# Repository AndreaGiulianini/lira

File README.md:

# Lira

> [!WARNING]
> **This keyboard has never been built.** It is a design only: no prototype of either version (wireless on branch
> `main`, wired on branch `rp2040`) has ever been ordered, assembled or powered on, and nothing here has been tested
> on real hardware. The circuit, PCB, case and firmware are generated and checked automatically and reviewed on paper,
> but passing those checks does not make a working board: there may be mistakes that only a real prototype would
> reveal. **Do not put it into production, sell it or order it in quantity.** If you build one anyway, treat it as an
> untested design: order the minimum quantity and expect to debug it yourself.

A 40% keyboard in the [KBDfans Agar Mini](https://kbdfans.com/products/agar-mini) layout, with a numpad on the
left and a split 3u + 3u spacebar.
USB-C, hot-swap MX switches, RMK firmware with Vial, and a built-in USB sound card (3.5 mm headset jack
at the back: headphones and microphone, with a headphone amplifier). 3D-printed case inspired by the Apple
M0110 (1984), top mount: the plate is screwed to the top frame and the PCB hangs from the switches, so no printed
part has to hold the PCB flat.

**Two versions of the same keyboard**, one per git branch, with the same layout, plate and sound card, and the same case and keymap apart from the battery pocket and the Bluetooth keys:

| Branch | Version | Microcontroller | Power |
|---|---|---|---|
| [`main`](../../tree/main) | wireless: Bluetooth + USB-C | Ebyte E73 module (nRF52840) | LiPo battery, or the cable alone |
| **`rp2040`** (this one) | **wired: USB-C only** | **Raspberry Pi RP2040** + 16 MB QSPI flash | **the cable, no battery** |

The sound card only ever works over the cable (there is no audio over Bluetooth here), so if the headset jack is
the point, the radio, the cell, the charger and the power switch are things you pay for and never use: this
version drops them. It is also simpler to build: the RP2040 programs itself over USB (no SWD probe, no bootloader
to flash), and there is no battery to buy and wire.

## Inspiration and credits

None of the ideas here are mine: this board is a combination of things other people made, plus the one thing I
always wanted and could not buy — a headset jack on a keyboard.

- **Layout** — the 40% block with the split 3u + 3u spacebar is KBDfans' [Agar Mini](https://kbdfans.com/products/agar-mini).
  The numpad on the left is my addition, and what makes it 57 keys.
- **Board** — the "40% + numpad in one flat rectangular case" idea and the overall proportions are inspired by the
  [**Lyra**](https://github.com/PiKeeb/lyra-keyboard), designed by **alexbarb** (case) with the PCB by **KGOH** and
  **ILWrites**. Lira is not a copy: it uses the Agar Mini body, a top-mount case and a completely different PCB.
- **The 3.5 mm headset jack** — laptop headphones + microphone built into the keyboard itself. The sound card follows
  C-Media's own CM108B reference design behind a CH334P USB hub (see
  `production/5-schematic-and-checks/differences-from-wireless.txt`).
- **Microcontroller** — Raspberry Pi's own minimum circuit for the RP2040 ("Hardware design with RP2040", the
  Pico's): crystal, flash, decoupling, BOOT and RESET. The wireless version's power, USB and programming follow the
  BlueMicro840 ([jpconstantineau/NRF52-Board](https://github.com/jpconstantineau/NRF52-Board)).
- **Case** — the shape and colour follow the Apple M0110 (1984).

Thanks to all of them.

## Where to find things

| Folder | What it contains |
|---|---|
| **[`production/`](production/README.md)** | Everything to build the 57-key keyboard: files for JLCPCB, plate, case to print, firmware, pictures |
| [`guide/`](guide/build-guide.md) | Complete guide: ordering from JLCPCB, what to buy, first programming, printing and assembly |
| [`source/`](source/README.md) | The code that generates everything: edit only here, then regenerate |

`production/` is **self-contained**: it holds everything needed to build the keyboard (the KiCad files use the footprint libraries in `source/lib/`)
and has its own README listing the files and what to do with them:

```
production/
├── README.md                what's inside and what to do with it
├── 1-pcb-jlcpcb/            gerber-pcb.zip, bom.csv, cpl.csv
├── 2-plate/                 the plate: JLCPCB (FR4 gerbers), laser cut (DXF) or 3D printed (2 STL)
├── 3-case-3d-print/         the 4 STL pieces (+ step/)
├── 4-firmware/              .uf2 firmware, vial.json, keyboard.toml
├── 5-schematic-and-checks/  schematic (PDF) and the results of the automatic checks
├── kicad/                   PCB, plate and schematic to open in KiCad
└── images/                  layout, Blender renders: on a desk, every side, exploded, PCB
```

> `production/` is **rewritten** on every regeneration: do not edit it by hand.

## How reliable it is

Everything below is checked on paper and in software, **not a tested board** (see the warning at the top).

The RP2040 circuit is Raspberry Pi's minimal design (the Pico's), with the crystal Raspberry Pi qualified for it;
everything else is the wireless board's (USB-C, ESD, hub, sound card, matrix). The differences are listed in
`5-schematic-and-checks/differences-from-wireless.txt`. The circuit, PCB, case and firmware are checked
automatically on every build:

- KiCad's ERC, a pin-by-pin check between circuit, PCB and schematic, and datasheet tests written independently of
  the design (`erc-kicad.txt`, `consistency-check.txt`, `datasheet-checks.txt`);
- a mechanical fit check of the case against the finished PCB (`fit-check.txt`).

These checks reduce the risk; they do not replace a prototype. The guide, §8, lists what to verify on the first
board.

## Small hardware

| Item | Quantity |
|---|---|
| M2 heat-set inserts (for a 3.2 mm hole, length 3 mm) | 6 (top frame: the plate's ears) |
| M2 × 5 mm socket-head screws (DIN 912) | 6 (plate to top frame) |
| Short M3 heat-set inserts (Ø ~4.5 mm, length 3 mm, for a 4.0 mm hole) | 11 (top frame) |
| M3 × 12 mm socket-head screws (DIN 912) | 8 (front and sides) |
| M3 × 20 mm socket-head screws (DIN 912) | 3 (back: through the PCB's holes and the plate's tabs) |
| Ø 3 × 14 mm alignment pins (steel rod or 3 mm filament) | 4 |
| Ø 12 mm rubber feet | 4 |
| Long 2.5 mm hex key (some M3 screw holes are 21 mm deep) and a 1.5 mm hex key (M2) | 1 + 1 |

## Printing the case

- No supports. **Top frames**: lying on their flat underside (the side the plate screws to), deck up: the STL files are exported tilted, as assembled, so use the slicer's “lay on face” on that flat underside. **Bottom halves**: placed the way they sit
  on the desk.
- PLA or PETG, 3 perimeters, 5 solid top layers and 4 bottom layers. Infill: **top frames** gyroid 15 %,
  **bottom halves** gyroid 8 % or lightning. The strength comes from the walls and the solid layers, not from
  the inside.
- Material (estimate, PLA): about 300–320 g this way, versus about 370 g with 15 % everywhere. The bottom halves
  are already 85 % empty inside: designing cavities into them would cost **more** (tried it: 290 g instead of
  273 g), because every cavity adds walls, a ceiling and ribs that print solid.
- For the fine texture of the M0110: light "fuzzy skin" (0.1 mm) on the outer surfaces, or textured spray
  paint.
- Reference colour: warm beige between `#C8C2A0` and `#D5D0B4` (Pantone 453 was the original).
- The case is split to fit a 256 mm bed: with a bigger printer, change `BED` in
  `source/case/gen_case.py` and regenerate.

## Editing and regenerating

Edit only `source/` (for example `layout.py` for the keys, `case/gen_case.py` for the case), then:

```sh
cd source
make all            # regenerates everything (about 25 minutes on an M4, most of it the Blender renders)
make pcb            # or a single step: see source/README.md
```

Technical details in [`source/README.md`](source/README.md).

## License

[MIT](LICENSE) — that covers everything in this repository that I made.

The firmware is built on [RMK](https://github.com/HaoboGu/rmk) and the embassy crates (MIT / Apache-2.0) and is configured with [Vial](https://get.vial.today) (GPL-2.0, used, not bundled).

Bundled third-party parts keep their own terms and are **not** relicensed by the above: `source/tools/KeyV2`
(GPL-3.0, a git submodule), Raspberry Pi's second-stage boot code in the firmware (BSD-3-Clause), the kiswitch footprints and 3D models under `source/lib/` (CC BY-SA 4.0), and the
vendor symbols/models (KiCad, LCSC). The [Lyra](https://github.com/PiKeeb/lyra-keyboard) and the KBDfans Agar Mini
are cited as inspiration only — no files from either are included here.

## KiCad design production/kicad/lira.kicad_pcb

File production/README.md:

# Lira

57 keys: numpad on the left + Agar mini 40% with a split 3u + 3u spacebar, built-in USB sound card. Wired version: USB-C only, no battery, Raspberry Pi RP2040.

> [!WARNING]
> **This keyboard has never been built.** It is a design only: no prototype of either version (wireless on branch
> `main`, wired on branch `rp2040`) has ever been ordered, assembled or powered on, and nothing here has been tested
> on real hardware. The circuit, PCB, case and firmware are generated and checked automatically and reviewed on paper,
> but passing those checks does not make a working board: there may be mistakes that only a real prototype would
> reveal. **Do not put it into production, sell it or order it in quantity.** If you build one anyway, treat it as an
> untested design: order the minimum quantity and expect to debug it yourself.

> This folder is **generated automatically** from `../source/` and is rewritten every time it is regenerated:
> do not edit it by hand.

## What is here and what to do with it

| Folder | Files | What to do with them |
|---|---|---|
| `1-pcb-jlcpcb/` | `gerber-pcb.zip`, `bom.csv`, `cpl.csv` | PCB order at JLCPCB: 2 layers, 1.6 mm, assembly of the **bottom side** (206 parts, 44 different part numbers). |
| `2-plate/` | | The plate carries the keyboard (6 ears and 3 back tabs screw it to the top frame). Three ways to make it, all interchangeable (guide, §2): |
| | `jlcpcb/gerber-plate.zip` | cut by JLCPCB: 1.6 mm FR4, ordered like a PCB with no copper and no assembly (black or white) |
| | `laser-cut/plate.dxf` | laser cut in metal or plastic (1.5 mm aluminium or steel, POM…), e.g. JLCCNC sheet metal |
| | `3d-print/plate-left.stl`, `plate-right.stl` | 3D printed (PLA/PETG) in two pieces, top face on the bed, no supports; 4 mm ribbed, 1.5 mm where the switches clip in |
| `3-case-3d-print/` | `bottom-left.stl`, `bottom-right.stl`, `top-left.stl`, `top-right.stl` | Case to print **without supports**: the top frames lying on their flat underside (the side the plate screws to), deck up: the STL files are exported tilted, as assembled, so use the slicer's “lay on face” on that flat underside, the bottom halves the way they sit on the desk. The same pieces for CAD are in `step/` |
| | `fit-check.txt` | Result of the automatic fit check: PCB, parts, plate, keys, screws and ports against the printed pieces (see guide, §7) |
| `4-firmware/` | `lira.uf2` | Firmware: a new board shows up as the **RPI-RP2** drive as soon as it is plugged in: drag the file onto it. To update it later: fn + Esc, or hold BOOT (paperclip, underside) while plugging the cable in (see guide §4) |
| | `vial.json`, `keyboard.toml` | Configuration (Vial reads it from the keyboard by itself; these are for reference only) |
| `5-schematic-and-checks/` | `schematic.pdf` | Circuit diagram, for anyone who wants to review the circuit (also `schematic.svg`) |
| | `differences-from-wireless.txt` | What changes from the wireless board (RP2040 after Raspberry Pi's own design, no battery), and the sound card's differences from the chip maker's reference design |
| | `erc-kicad.txt`, `consistency-check.txt`, `datasheet-checks.txt` | Results of the three automatic checks (see guide, §6) |
| | `netlist.json` | Every connection, pin by pin, in readable form |
| `kicad/` | `lira.kicad_pcb`, `plate.kicad_pcb`, `schematic/` | To open the PCB, plate and schematic in KiCad |
| `images/` | pictures | Layout; Blender Cycles renders: the keyboard on a desk (`desk.jpg`), the case from every side, an exploded view, the PCB |

## Summary

- 57 hot-swap MX switches, USB-C, Raspberry Pi RP2040, RMK firmware with Vial. Wired: no battery, no Bluetooth (the
  wireless version, with an nRF52840 and a LiPo cell, is on the git branch `main`).
- Built-in USB sound card: a 3.5 mm headset jack at the back (headphones + microphone, CTIA plugs) with a headphone
  amplifier, behind a USB hub; over the USB cable the computer sees a keyboard and a USB headset (no drivers). The
  firmware turns it on once the computer has set the keyboard up, and the amplifier off while the computer sleeps and
  as soon as the cable starts to be pulled out (no click).
- Case in 4 pieces to print (256 mm bed), inspired by the Apple M0110; top mount (plate screwed to the top frame).

## Buy separately

| What | Notes |
|---|---|
| 57 MX switches + keycaps (Agar mini set + numpad kit) | you need a 2u vertical Enter, a 2u 0, a 1u + and a 1u − (most numpad kits only have a 2u +) |
| Screw-in PCB stabilizers: 2 × 2u + 2 for the 3u bars | 3u wire with 38.1 mm spacing |
| Screws, heat-set inserts, pins, feet | list in `../README.md` |

Every step in detail: [`../guide/build-guide.md`](../guide/build-guide.md).

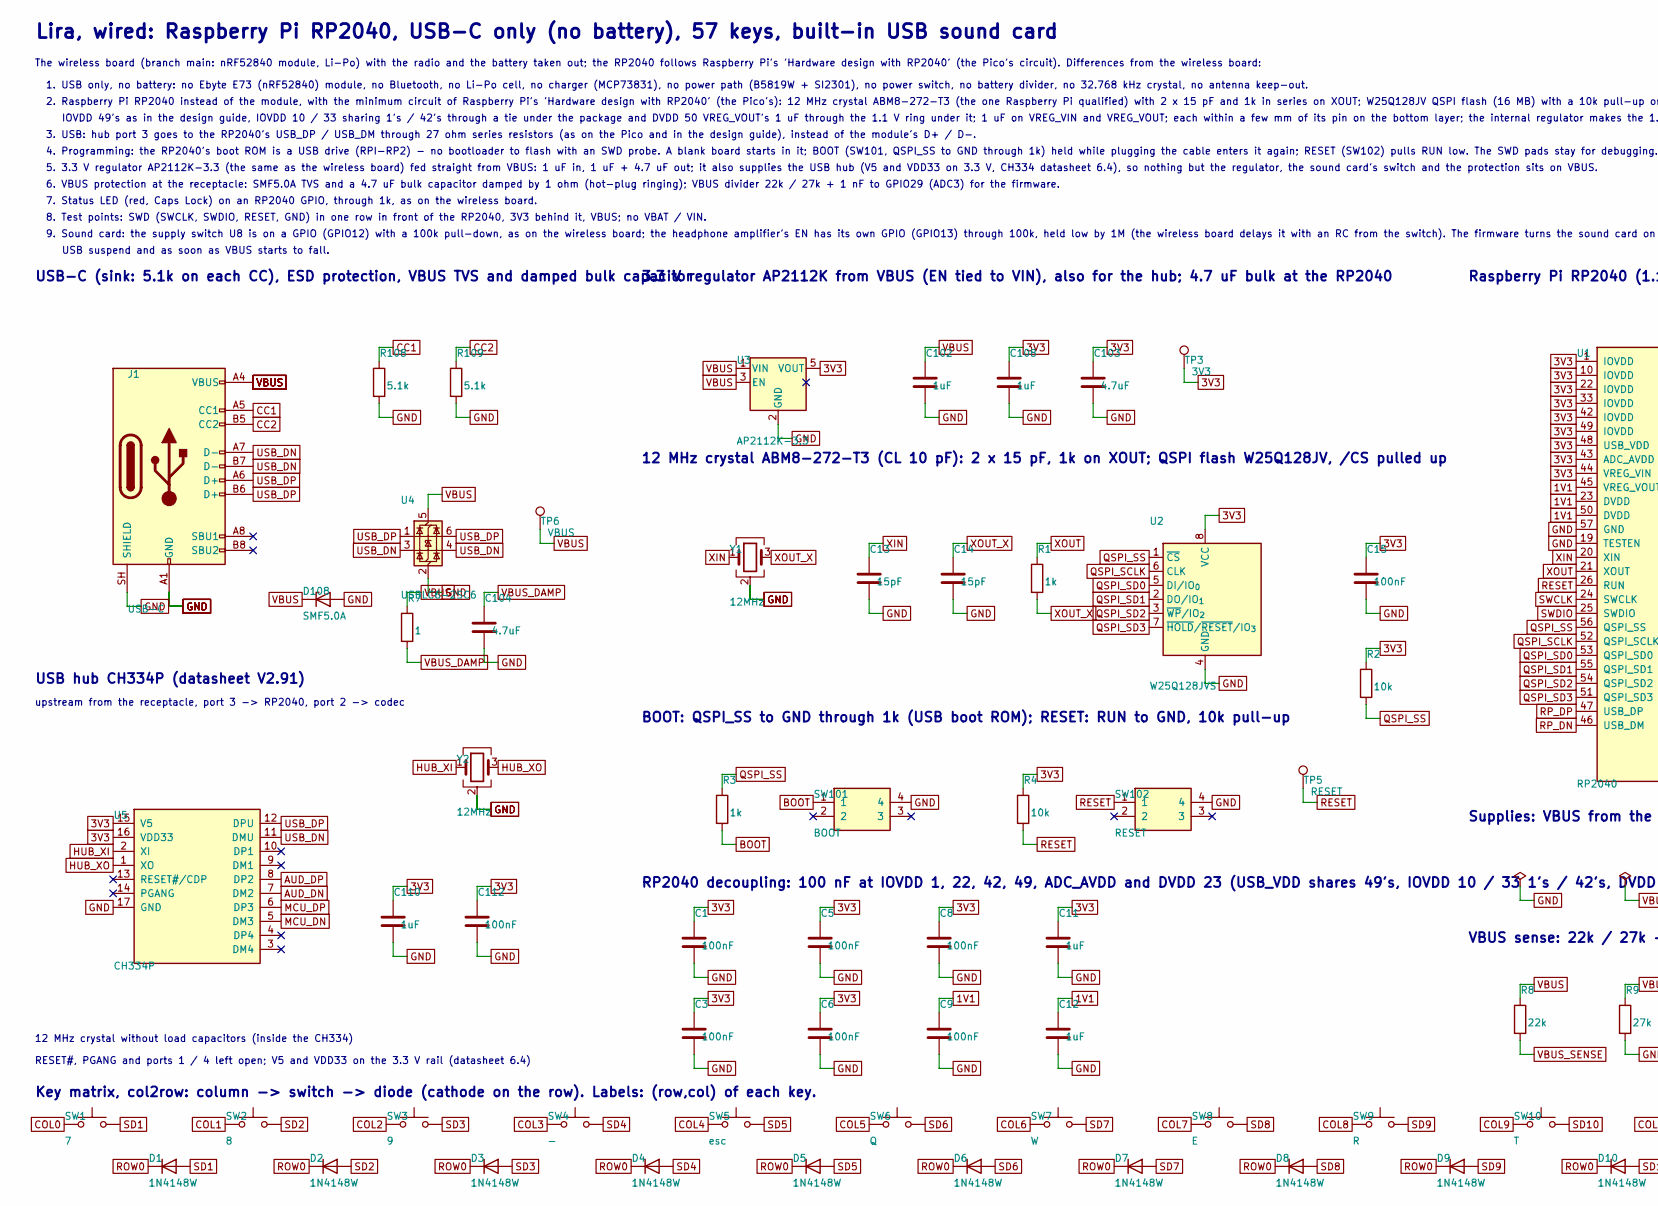
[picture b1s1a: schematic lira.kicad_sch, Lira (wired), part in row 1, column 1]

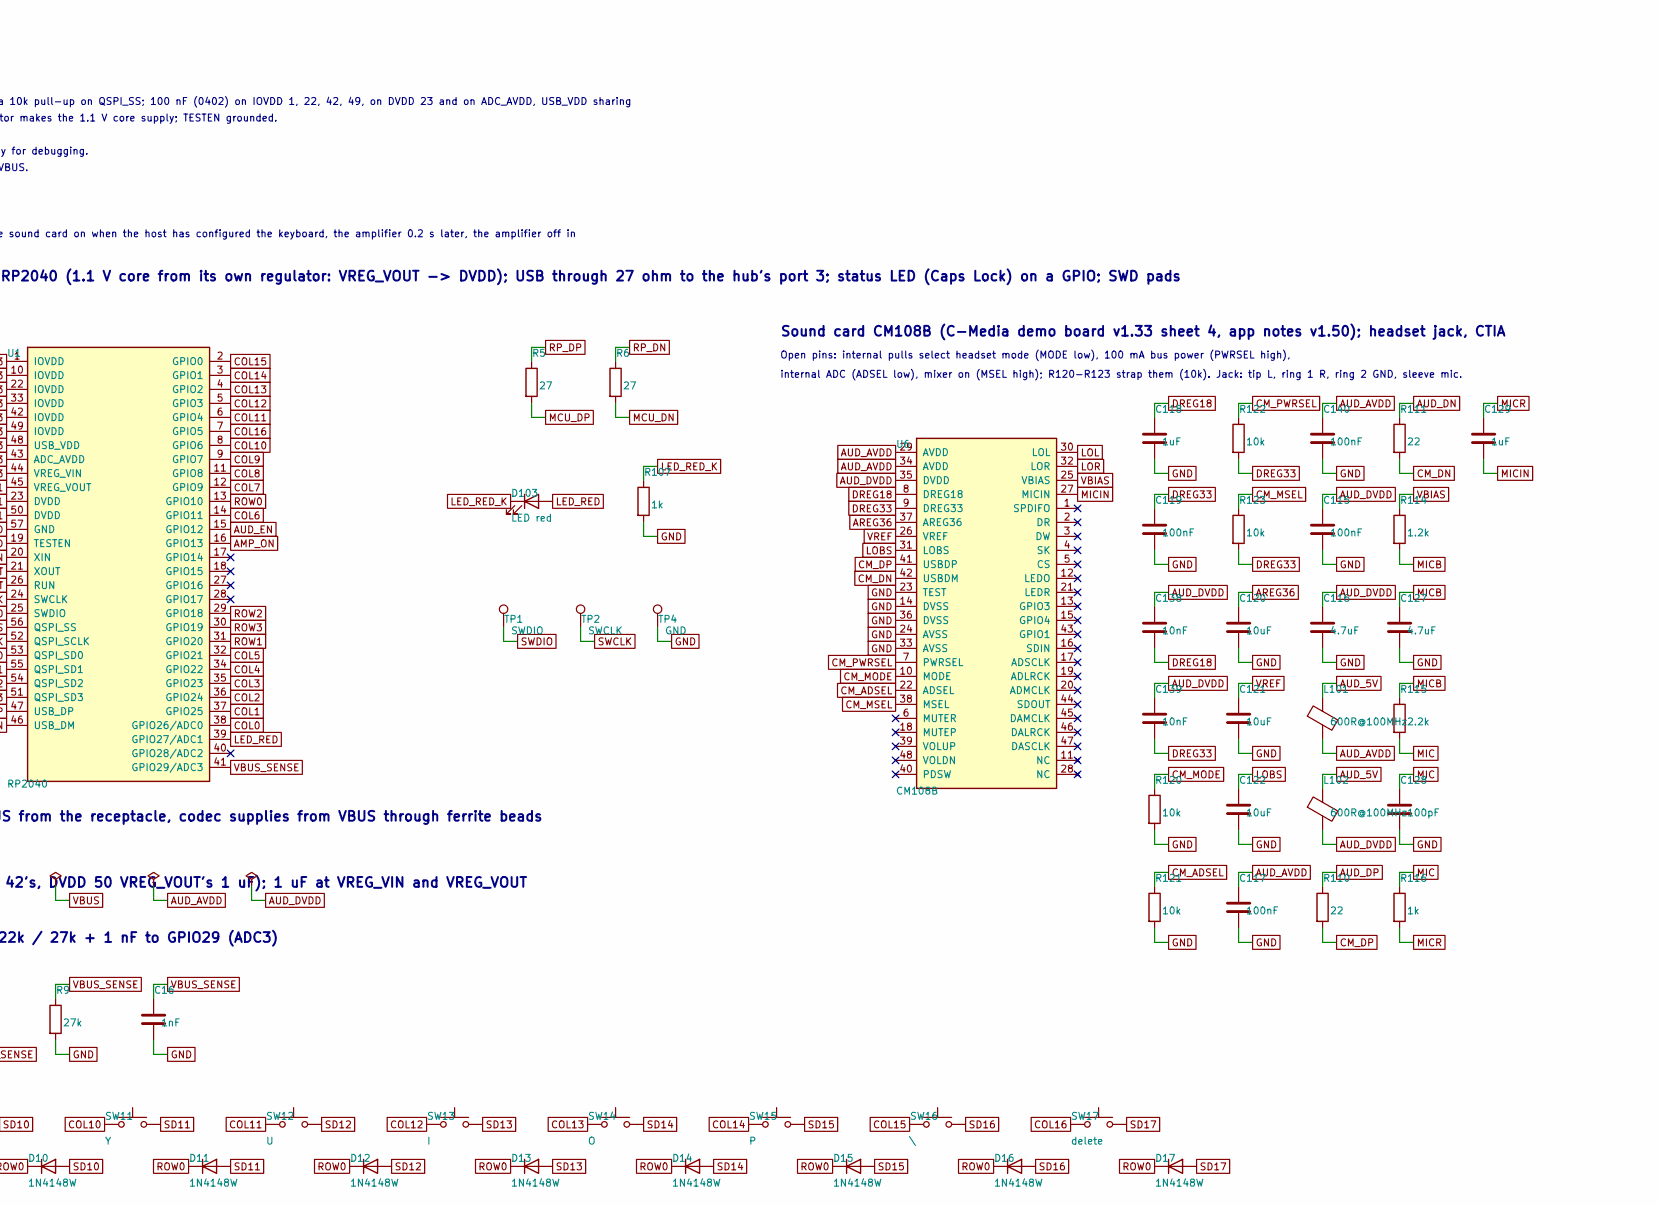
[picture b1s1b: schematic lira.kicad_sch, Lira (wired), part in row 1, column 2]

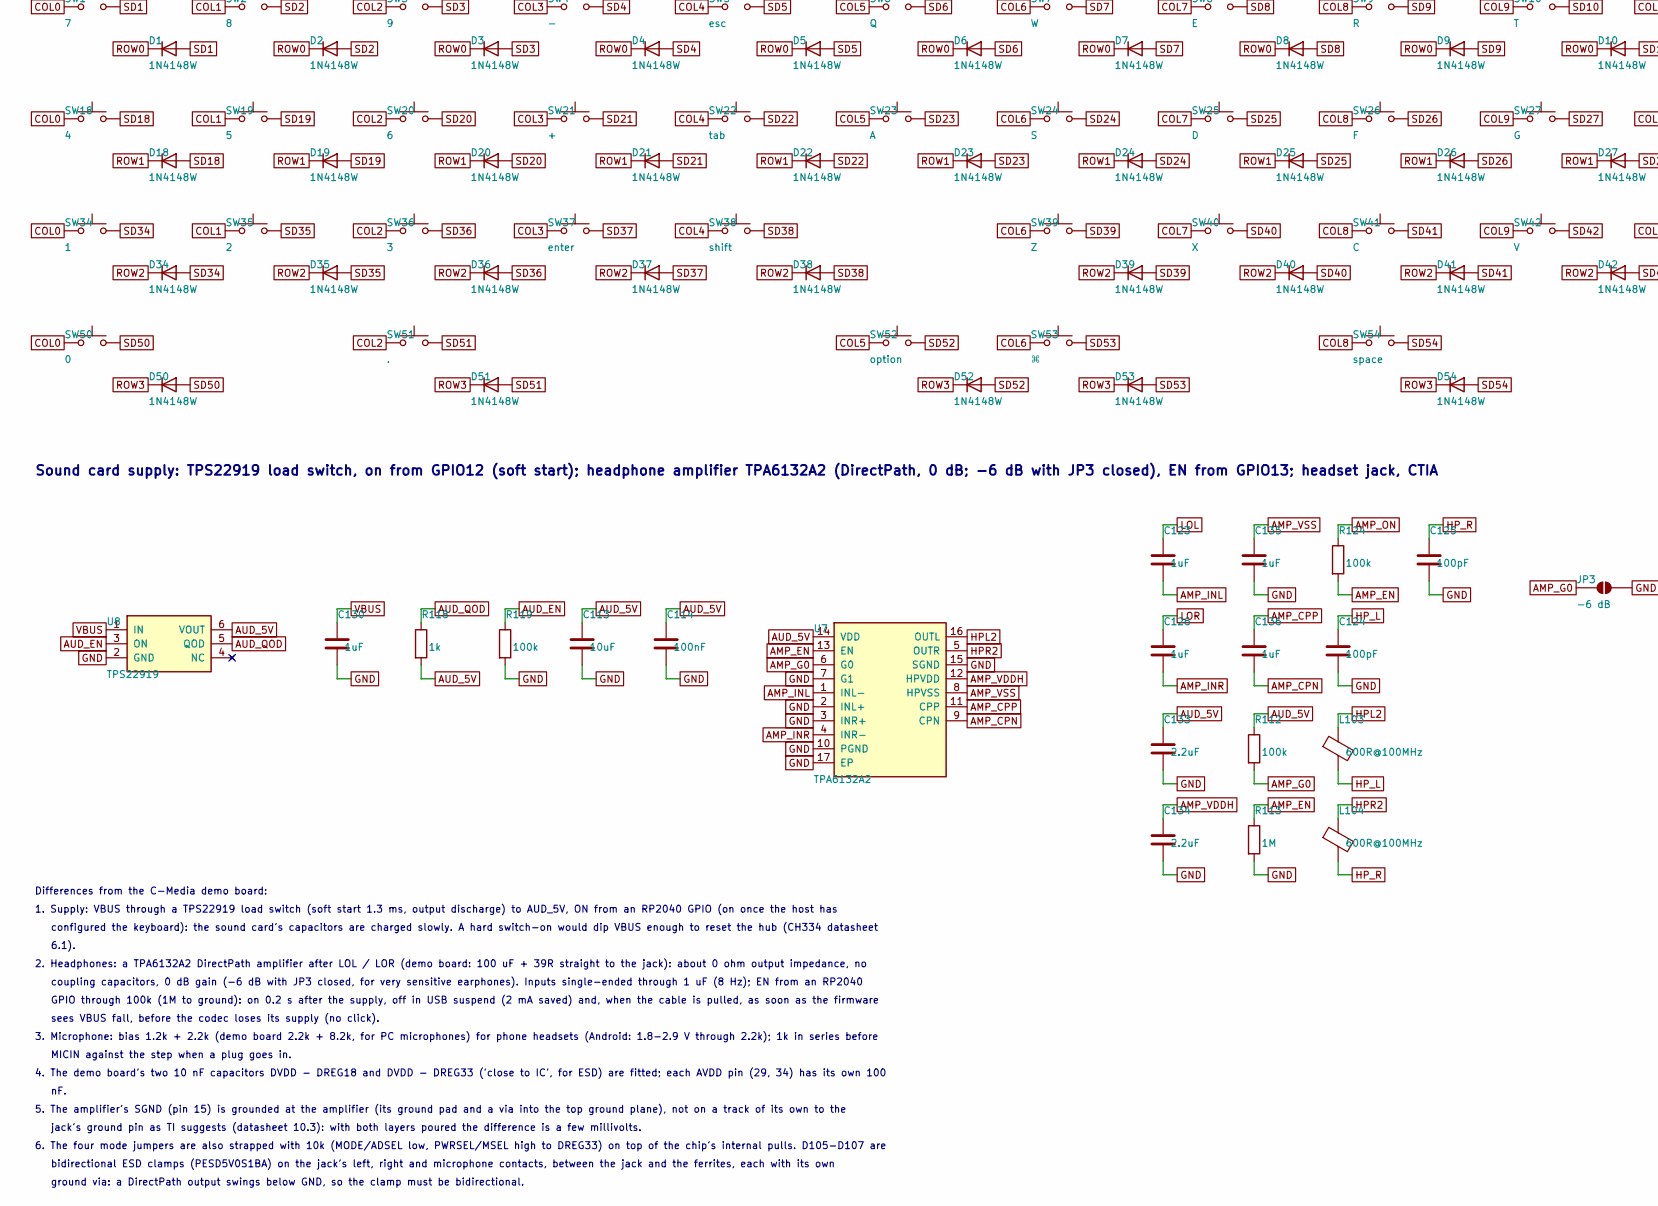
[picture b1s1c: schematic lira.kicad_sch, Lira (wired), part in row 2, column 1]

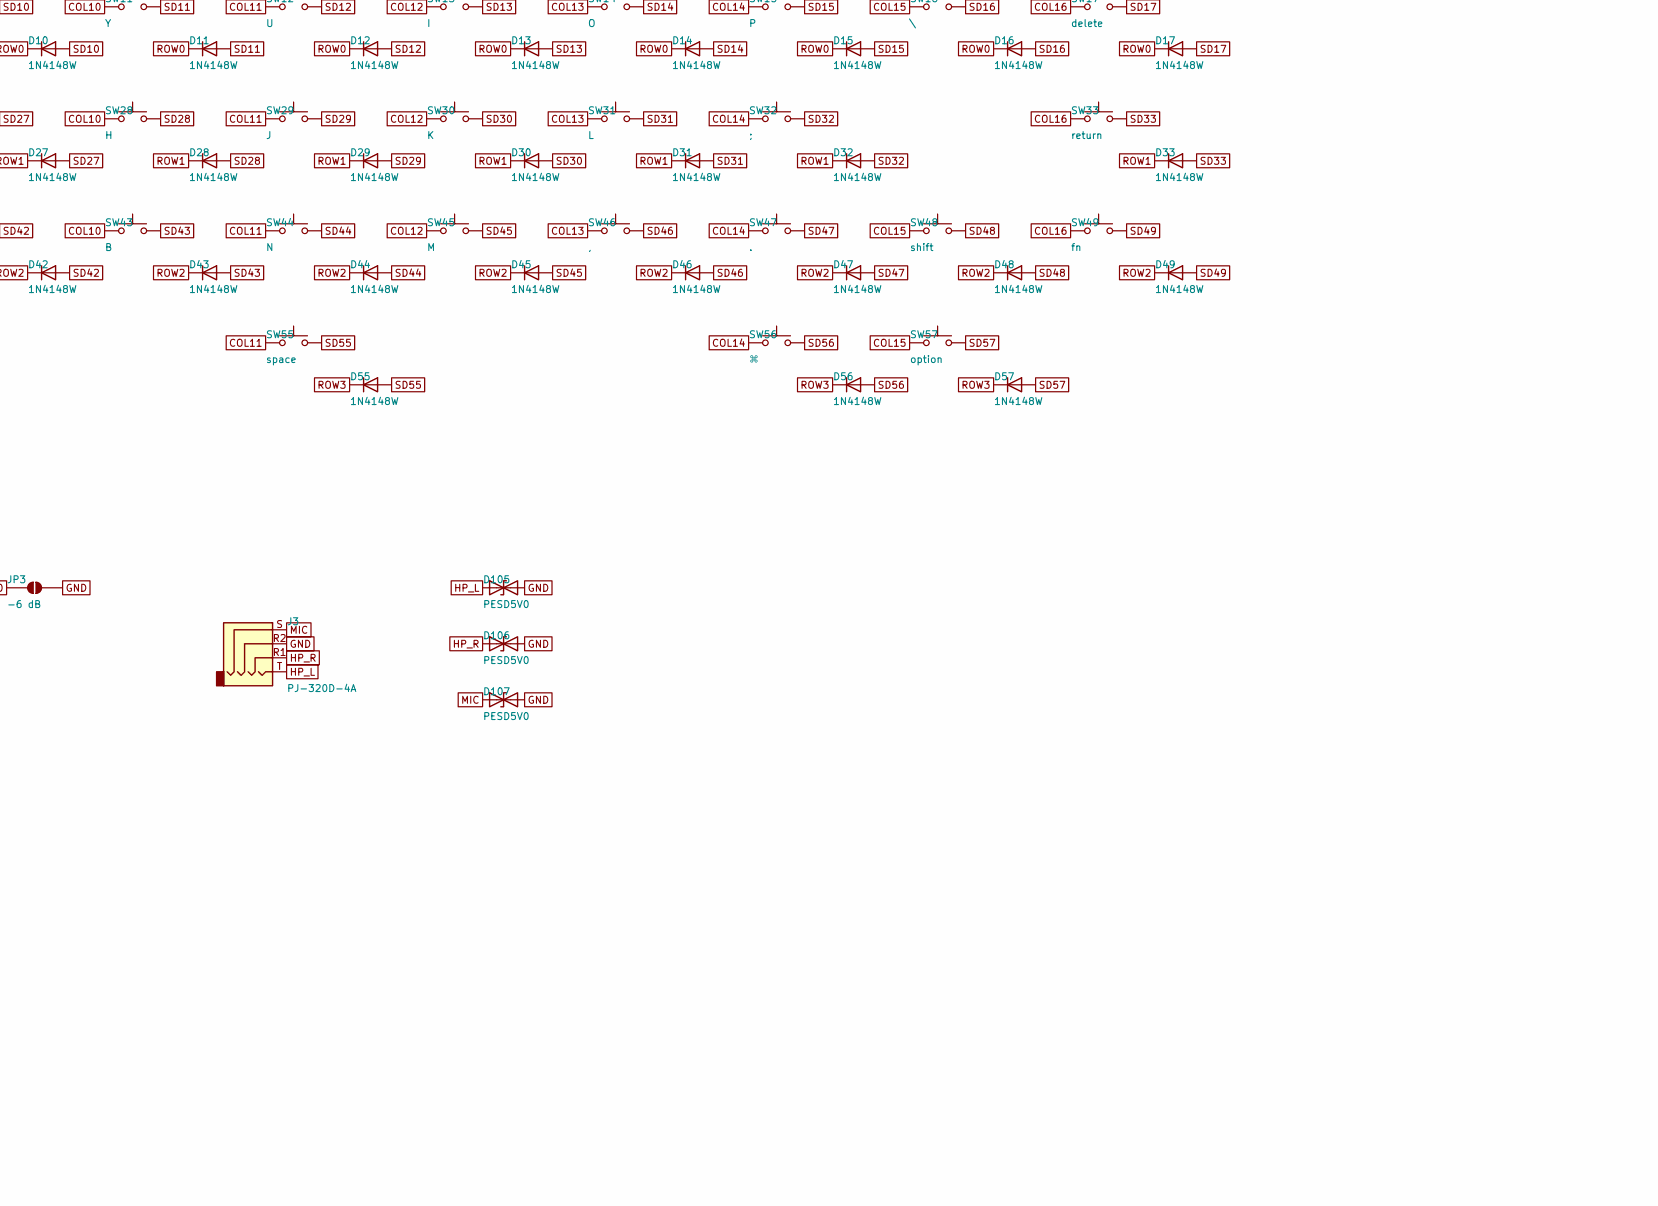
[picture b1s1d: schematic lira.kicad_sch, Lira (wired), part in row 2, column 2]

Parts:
C1, C3, C5, C6, C8, C9, C140: 100nF; C_0402_1005Metric; LCSC C1525
C11, C12: 1uF; C_0402_1005Metric; LCSC C52923
C13, C14: 15pF; C_0402_1005Metric; LCSC C1548
C15, C112, C114, C115, C117, C119: 100nF; C_0603_1608Metric; LCSC C14663
C16: 1nF; C_0603_1608Metric; LCSC C1588
C102, C108, C110, C118, C123, C126, C129, C130, C135, C136: 1uF; C_0603_1608Metric; LCSC C15849
C103, C116, C127: 4.7uF; C_0603_1608Metric; LCSC C19666
C104: 4.7uF; C_0805_2012Metric; LCSC C1779
C113, C120, C121, C122: 10uF; C_0603_1608Metric; LCSC C19702
C124, C125, C128: 100pF; C_0603_1608Metric; LCSC C14858
C133, C134: 2.2uF; C_0603_1608Metric; LCSC C23630
C138, C139: 10nF; C_0603_1608Metric; LCSC C57112
D1, D2, D3, D4, D5, D6, D7, D8, D9, D10, D11, D12, D13, D14, D15, D16, D17, D18, D19, D20, D21, D22, D23, D24, D25, D26, D27, D28, D29, D30, D31, D32, D33, D34, D35, D36, D37, D38, D39, D40, D41, D42, D43, D44, D45, D46, D47, D48, D49, D50, D51, D52, D53, D54, D55, D56, D57: 1N4148W; D_SOD-123; LCSC C81598
D103: LED red; LED_0603_1608Metric; LCSC C2286
D105, D106, D107: PESD5V0; D_SOD-323; LCSC C19224
D108: SMF5.0A; D_SOD-123F; LCSC C2857263
J1: USB-C; USB_C_Receptacle_HRO_TYPE-C-31-M-12; LCSC C165948
J3: PJ-320D-4A; Jack_3.5mm_KoreanHropartsElec_PJ-320D-4A_Horizontal; LCSC C95562
JP3: -6 dB; SolderJumper-2_P1.3mm_Open_RoundedPad1.0x1.5mm
L101, L102, L103, L104: 600R@100MHz; L_0603_1608Metric; LCSC C1002
R1: 1k; R_0402_1005Metric; LCSC C11702
R2, R4, R120, R121, R122, R123: 10k; R_0603_1608Metric; LCSC C25804
R3, R107, R116, R118: 1k; R_0603_1608Metric; LCSC C21190
R5, R6: 27; R_0402_1005Metric; LCSC C2909343
R7: 1; R_0603_1608Metric; LCSC C22936
R8: 22k; R_0603_1608Metric; LCSC C31850
R9: 27k; R_0603_1608Metric; LCSC C22967
R108, R109: 5.1k; R_0603_1608Metric; LCSC C23186
R110, R111: 22; R_0603_1608Metric; LCSC C23345
R112, R119, R124: 100k; R_0603_1608Metric; LCSC C25803
R113: 1M; R_0603_1608Metric; LCSC C22935
R114: 1.2k; R_0603_1608Metric; LCSC C22765
R115: 2.2k; R_0603_1608Metric; LCSC C4190
SW1: 7; SW_Hotswap_Kailh_MX_1.00u; LCSC C41430893
SW2: 8; SW_Hotswap_Kailh_MX_1.00u; LCSC C41430893
SW3: 9; SW_Hotswap_Kailh_MX_1.00u; LCSC C41430893
SW4: −; SW_Hotswap_Kailh_MX_1.00u; LCSC C41430893
SW5: esc; SW_Hotswap_Kailh_MX_1.00u; LCSC C41430893
SW6: Q; SW_Hotswap_Kailh_MX_1.00u; LCSC C41430893
SW7: W; SW_Hotswap_Kailh_MX_1.00u; LCSC C41430893
SW8: E; SW_Hotswap_Kailh_MX_1.00u; LCSC C41430893
SW9: R; SW_Hotswap_Kailh_MX_1.00u; LCSC C41430893
SW10: T; SW_Hotswap_Kailh_MX_1.00u; LCSC C41430893
SW11: Y; SW_Hotswap_Kailh_MX_1.00u; LCSC C41430893
SW12: U; SW_Hotswap_Kailh_MX_1.00u; LCSC C41430893
SW13: I; SW_Hotswap_Kailh_MX_1.00u; LCSC C41430893
SW14: O; SW_Hotswap_Kailh_MX_1.00u; LCSC C41430893
SW15: P; SW_Hotswap_Kailh_MX_1.00u; LCSC C41430893
SW16: \; SW_Hotswap_Kailh_MX_1.00u; LCSC C41430893
SW17: delete; SW_Hotswap_Kailh_MX_1.00u; LCSC C41430893
SW18: 4; SW_Hotswap_Kailh_MX_1.00u; LCSC C41430893
SW19: 5; SW_Hotswap_Kailh_MX_1.00u; LCSC C41430893
SW20: 6; SW_Hotswap_Kailh_MX_1.00u; LCSC C41430893
SW21: +; SW_Hotswap_Kailh_MX_1.00u; LCSC C41430893
SW22: tab; SW_Hotswap_Kailh_MX_1.25u; LCSC C41430893
SW23: A; SW_Hotswap_Kailh_MX_1.00u; LCSC C41430893
SW24: S; SW_Hotswap_Kailh_MX_1.00u; LCSC C41430893
SW25: D; SW_Hotswap_Kailh_MX_1.00u; LCSC C41430893
SW26: F; SW_Hotswap_Kailh_MX_1.00u; LCSC C41430893
SW27: G; SW_Hotswap_Kailh_MX_1.00u; LCSC C41430893
SW28: H; SW_Hotswap_Kailh_MX_1.00u; LCSC C41430893
SW29: J; SW_Hotswap_Kailh_MX_1.00u; LCSC C41430893
SW30: K; SW_Hotswap_Kailh_MX_1.00u; LCSC C41430893
SW31: L; SW_Hotswap_Kailh_MX_1.00u; LCSC C41430893
SW32: ;; SW_Hotswap_Kailh_MX_1.00u; LCSC C41430893
SW33: return; SW_Hotswap_Kailh_MX_1.75u; LCSC C41430893
SW34: 1; SW_Hotswap_Kailh_MX_1.00u; LCSC C41430893
SW35: 2; SW_Hotswap_Kailh_MX_1.00u; LCSC C41430893
SW36: 3; SW_Hotswap_Kailh_MX_1.00u; LCSC C41430893
SW37: enter; SW_Hotswap_Kailh_MX_2.00u_90deg; LCSC C41430893
SW38: shift; SW_Hotswap_Kailh_MX_1.75u; LCSC C41430893
SW39: Z; SW_Hotswap_Kailh_MX_1.00u; LCSC C41430893
SW40: X; SW_Hotswap_Kailh_MX_1.00u; LCSC C41430893
SW41: C; SW_Hotswap_Kailh_MX_1.00u; LCSC C41430893
SW42: V; SW_Hotswap_Kailh_MX_1.00u; LCSC C41430893
SW43: B; SW_Hotswap_Kailh_MX_1.00u; LCSC C41430893
SW44: N; SW_Hotswap_Kailh_MX_1.00u; LCSC C41430893
SW45: M; SW_Hotswap_Kailh_MX_1.00u; LCSC C41430893
SW46: ,; SW_Hotswap_Kailh_MX_1.00u; LCSC C41430893
SW47, SW51: .; SW_Hotswap_Kailh_MX_1.00u; LCSC C41430893
SW48: shift; SW_Hotswap_Kailh_MX_1.25u; LCSC C41430893
SW49: fn; SW_Hotswap_Kailh_MX_1.00u; LCSC C41430893
SW50: 0; SW_Hotswap_Kailh_MX_2.00u; LCSC C41430893
SW52, SW57: option; SW_Hotswap_Kailh_MX_1.00u; LCSC C41430893
SW53, SW56: ⌘; SW_Hotswap_Kailh_MX_1.25u; LCSC C41430893
SW54, SW55: space; SW_Hotswap_Kailh_MX_3.00u; LCSC C41430893
SW101: BOOT; SW-SMD_4P-L5.1-W5.1-P3.70-LS6.5-TL_H1.5; LCSC C318884
SW102: RESET; SW-SMD_4P-L5.1-W5.1-P3.70-LS6.5-TL_H1.5; LCSC C318884
TP1: SWDIO; TestPoint_Pad_D1.0mm
TP2: SWCLK; TestPoint_Pad_D1.0mm
TP3: 3V3; TestPoint_Pad_D1.0mm
TP4: GND; TestPoint_Pad_D1.0mm
TP5: RESET; TestPoint_Pad_D1.0mm
TP6: VBUS; TestPoint_Pad_D1.5mm
U1: RP2040; QFN-56-1EP_7x7mm_P0.4mm_EP3.2x3.2mm; LCSC C2040
U2: W25Q128JVS; SOIC-8_5.3x5.3mm_P1.27mm; LCSC C97521
U3: AP2112K-3.3; SOT-23-5; LCSC C51118
U4: USBLC6-2SC6; SOT-23-6; LCSC C7519
U5: CH334P; WCH_QFN-16-1EP_3x3mm_P0.5mm_EP1.8x1.8mm; LCSC C5373042
U6: CM108B; LQFP-48_7x7mm_P0.5mm; LCSC C371347
U7: TPA6132A2; WQFN-16-1EP_3x3mm_P0.5mm_EP1.68x1.68mm; LCSC C69901
U8: TPS22919; SOT-363_SC-70-6; LCSC C2149796
Y1: 12MHz; Crystal_SMD_3225-4Pin_3.2x2.5mm; LCSC C20625731
Y2: 12MHz; Crystal_SMD_3225-4Pin_3.2x2.5mm; LCSC C9002

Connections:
1V1: C9.1, C12.1, U1.23 (DVDD), U1.45 (VREG_VOUT), U1.50 (DVDD)
3V3: C1.1, C3.1, C5.1, C6.1, C8.1, C11.1, C15.1, C103.1, C108.1, C110.1, C112.1, R2.1, R4.1, TP3.1, U1.1 (IOVDD), U1.10 (IOVDD), U1.22 (IOVDD), U1.33 (IOVDD), U1.42 (IOVDD), U1.43 (ADC_AVDD), U1.44 (VREG_VIN), U1.48 (USB_VDD), U1.49 (IOVDD), U2.8 (VCC), U3.5 (VOUT), U5.15 (V5), U5.16 (VDD33)
AMP_CPN: C136.2, U7.9 (CPN)
AMP_CPP: C136.1, U7.11 (CPP)
AMP_EN: R113.1, R124.2, U7.13 (EN)
AMP_G0: JP3.1 (A), R112.2, U7.6 (G0)
AMP_INL: C123.2, U7.1 (INL-)
AMP_INR: C126.2, U7.4 (INR-)
AMP_ON: R124.1, U1.16 (GPIO13)
AMP_VDDH: C134.1, U7.12 (HPVDD)
AMP_VSS: C135.1, U7.8 (HPVSS)
AREG36: C120.1, U6.37 (AREG36)
AUD_5V: C113.1, C114.1, C133.1, L101.1, L102.1, R112.1, R118.2, U7.14 (VDD), U8.6 (VOUT)
AUD_AVDD: C117.1, C140.1, L101.2, U6.29 (AVDD), U6.34 (AVDD)
AUD_DN: R111.1, U5.7 (DM2)
AUD_DP: R110.1, U5.8 (DP2)
AUD_DVDD: C115.1, C116.1, C138.1, C139.1, L102.2, U6.35 (DVDD)
AUD_EN: R119.1, U1.15 (GPIO12), U8.3 (ON)
AUD_QOD: R118.1, U8.5 (QOD)
BOOT: R3.2, SW101.1
CC1: J1.A5 (CC1), R108.1
CC2: J1.B5 (CC2), R109.1
CM_ADSEL: R121.1, U6.22 (ADSEL)
CM_DN: R111.2, U6.42 (USBDM)
CM_DP: R110.2, U6.41 (USBDP)
CM_MODE: R120.1, U6.10 (MODE)
CM_MSEL: R123.1, U6.38 (MSEL)
CM_PWRSEL: R122.1, U6.7 (PWRSEL)
COL0: SW1.1, SW18.1, SW34.1, SW50.1, U1.38 (GPIO26/ADC0)
COL1: SW2.1, SW19.1, SW35.1, U1.37 (GPIO25)
COL2: SW3.1, SW20.1, SW36.1, SW51.1, U1.36 (GPIO24)
COL3: SW4.1, SW21.1, SW37.1, U1.35 (GPIO23)
COL4: SW5.1, SW22.1, SW38.1, U1.34 (GPIO22)
COL5: SW6.1, SW23.1, SW52.1, U1.32 (GPIO21)
COL6: SW7.1, SW24.1, SW39.1, SW53.1, U1.14 (GPIO11)
COL7: SW8.1, SW25.1, SW40.1, U1.12 (GPIO9)
COL8: SW9.1, SW26.1, SW41.1, SW54.1, U1.11 (GPIO8)
COL9: SW10.1, SW27.1, SW42.1, U1.9 (GPIO7)
COL10: SW11.1, SW28.1, SW43.1, U1.8 (GPIO6)
COL11: SW12.1, SW29.1, SW44.1, SW55.1, U1.6 (GPIO4)
COL12: SW13.1, SW30.1, SW45.1, U1.5 (GPIO3)
COL13: SW14.1, SW31.1, SW46.1, U1.4 (GPIO2)
COL14: SW15.1, SW32.1, SW47.1, SW56.1, U1.3 (GPIO1)
COL15: SW16.1, SW48.1, SW57.1, U1.2 (GPIO0)
COL16: SW17.1, SW33.1, SW49.1, U1.7 (GPIO5)
DREG18: C118.1, C138.2, U6.8 (DREG18)
DREG33: C119.1, C139.2, R122.2, R123.2, U6.9 (DREG33)
GND: C1.2, C3.2, C5.2, C6.2, C8.2, C9.2, C11.2, C12.2, C13.2, C14.2, C15.2, C16.2, C102.2, C103.2, C104.2, C108.2, C110.2, C112.2, C113.2, C114.2, C115.2, C116.2, C117.2, C118.2, C119.2, C120.2, C121.2, C122.2, C124.2, C125.2, C127.2, C128.2, C130.2, C133.2, C134.2, C135.2, C140.2, D105.2 (A2), D106.2 (A2), D107.2 (A2), D108.2 (A), J1.A1 (GND), J1.A12 (GND), J1.B1 (GND), J1.B12 (GND), J1.SH (SHIELD), J3.R2, JP3.2 (B), R9.2, R107.2, R108.2, R109.2, R113.2, R119.2, R120.2, R121.2, SW101.4, SW102.4, TP4.1, U1.19 (TESTEN), U1.57 (GND), U2.4 (GND), U3.2 (GND), U4.2 (GND), U5.17 (GND), U6.14 (DVSS), U6.23 (TEST), U6.24 (AVSS), U6.33 (AVSS), U6.36 (DVSS), U7.2 (INL+), U7.3 (INR+), U7.7 (G1), U7.10 (PGND), U7.15 (SGND), U7.17 (EP), U8.2 (GND), Y1.2 (G), Y1.4 (G), Y2.2 (G), Y2.4 (G)
HPL2: L103.1, U7.16 (OUTL)
HPR2: L104.1, U7.5 (OUTR)
HP_L: C124.1, D105.1 (A1), J3.T, L103.2
HP_R: C125.1, D106.1 (A1), J3.R1, L104.2
HUB_XI: U5.2 (XI), Y2.1
HUB_XO: U5.1 (XO), Y2.3
LED_RED: D103.2 (A), U1.39 (GPIO27/ADC1)
LED_RED_K: D103.1 (K), R107.1
LOBS: C122.1, U6.31 (LOBS)
LOL: C123.1, U6.30 (LOL)
LOR: C126.1, U6.32 (LOR)
MCU_DN: R6.2, U5.5 (DM3)
MCU_DP: R5.2, U5.6 (DP3)
MIC: C128.1, D107.1 (A1), J3.S, R115.2, R116.1
MICB: C127.1, R114.2, R115.1
MICIN: C129.2, U6.27 (MICIN)
MICR: C129.1, R116.2
QSPI_SCLK: U1.52 (QSPI_SCLK), U2.6 (CLK)
QSPI_SD0: U1.53 (QSPI_SD0), U2.5 (DI/IO_{0})
QSPI_SD1: U1.55 (QSPI_SD1), U2.2 (DO/IO_{1})
QSPI_SD2: U1.54 (QSPI_SD2), U2.3 (~WP/IO_{2})
QSPI_SD3: U1.51 (QSPI_SD3), U2.7 (~HOLD/~RESET/IO_{3})
QSPI_SS: R2.2, R3.1, U1.56 (QSPI_SS), U2.1 (~CS)
RESET: R4.2, SW102.1, TP5.1, U1.26 (RUN)
ROW0: D1.1 (K), D2.1 (K), D3.1 (K), D4.1 (K), D5.1 (K), D6.1 (K), D7.1 (K), D8.1 (K), D9.1 (K), D10.1 (K), D11.1 (K), D12.1 (K), D13.1 (K), D14.1 (K), D15.1 (K), D16.1 (K), D17.1 (K), U1.13 (GPIO10)
ROW1: D18.1 (K), D19.1 (K), D20.1 (K), D21.1 (K), D22.1 (K), D23.1 (K), D24.1 (K), D25.1 (K), D26.1 (K), D27.1 (K), D28.1 (K), D29.1 (K), D30.1 (K), D31.1 (K), D32.1 (K), D33.1 (K), U1.31 (GPIO20)
ROW2: D34.1 (K), D35.1 (K), D36.1 (K), D37.1 (K), D38.1 (K), D39.1 (K), D40.1 (K), D41.1 (K), D42.1 (K), D43.1 (K), D44.1 (K), D45.1 (K), D46.1 (K), D47.1 (K), D48.1 (K), D49.1 (K), U1.29 (GPIO18)
ROW3: D50.1 (K), D51.1 (K), D52.1 (K), D53.1 (K), D54.1 (K), D55.1 (K), D56.1 (K), D57.1 (K), U1.30 (GPIO19)
RP_DN: R6.1, U1.46 (USB_DM)
RP_DP: R5.1, U1.47 (USB_DP)
SD1: D1.2 (A), SW1.2
SD2: D2.2 (A), SW2.2
SD3: D3.2 (A), SW3.2
SD4: D4.2 (A), SW4.2
SD5: D5.2 (A), SW5.2
SD6: D6.2 (A), SW6.2
SD7: D7.2 (A), SW7.2
SD8: D8.2 (A), SW8.2
SD9: D9.2 (A), SW9.2
SD10: D10.2 (A), SW10.2
SD11: D11.2 (A), SW11.2
SD12: D12.2 (A), SW12.2
SD13: D13.2 (A), SW13.2
SD14: D14.2 (A), SW14.2
SD15: D15.2 (A), SW15.2
SD16: D16.2 (A), SW16.2
SD17: D17.2 (A), SW17.2
SD18: D18.2 (A), SW18.2
SD19: D19.2 (A), SW19.2
SD20: D20.2 (A), SW20.2
SD21: D21.2 (A), SW21.2
SD22: D22.2 (A), SW22.2
SD23: D23.2 (A), SW23.2
SD24: D24.2 (A), SW24.2
SD25: D25.2 (A), SW25.2
SD26: D26.2 (A), SW26.2
SD27: D27.2 (A), SW27.2
SD28: D28.2 (A), SW28.2
SD29: D29.2 (A), SW29.2
SD30: D30.2 (A), SW30.2
SD31: D31.2 (A), SW31.2
SD32: D32.2 (A), SW32.2
SD33: D33.2 (A), SW33.2
SD34: D34.2 (A), SW34.2
SD35: D35.2 (A), SW35.2
SD36: D36.2 (A), SW36.2
SD37: D37.2 (A), SW37.2
SD38: D38.2 (A), SW38.2
SD39: D39.2 (A), SW39.2
SD40: D40.2 (A), SW40.2
SD41: D41.2 (A), SW41.2
SD42: D42.2 (A), SW42.2
SD43: D43.2 (A), SW43.2
SD44: D44.2 (A), SW44.2
SD45: D45.2 (A), SW45.2
SD46: D46.2 (A), SW46.2
SD47: D47.2 (A), SW47.2
SD48: D48.2 (A), SW48.2
SD49: D49.2 (A), SW49.2
SD50: D50.2 (A), SW50.2
SD51: D51.2 (A), SW51.2
SD52: D52.2 (A), SW52.2
SD53: D53.2 (A), SW53.2
SD54: D54.2 (A), SW54.2
SD55: D55.2 (A), SW55.2
SD56: D56.2 (A), SW56.2
SD57: D57.2 (A), SW57.2
SWCLK: TP2.1, U1.24 (SWCLK)
SWDIO: TP1.1, U1.25 (SWDIO)
USB_DN: J1.A7 (D-), J1.B7 (D-), U4.3 (I/O2), U4.4 (I/O2), U5.11 (DMU)
USB_DP: J1.A6 (D+), J1.B6 (D+), U4.1 (I/O1), U4.6 (I/O1), U5.12 (DPU)
VBIAS: R114.1, U6.25 (VBIAS)
VBUS: C102.1, C130.1, D108.1 (K), J1.A4 (VBUS), J1.A9 (VBUS), J1.B4 (VBUS), J1.B9 (VBUS), R7.1, R8.1, TP6.1, U3.1 (VIN), U3.3 (EN), U4.5 (VBUS), U8.1 (IN)
VBUS_DAMP: C104.1, R7.2
VBUS_SENSE: C16.1, R8.2, R9.1, U1.41 (GPIO29/ADC3)
VREF: C121.1, U6.26 (VREF)
XIN: C13.1, U1.20 (XIN), Y1.1
XOUT: R1.1, U1.21 (XOUT)
XOUT_X: C14.1, R1.2, Y1.3

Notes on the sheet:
Lira, wired: Raspberry Pi RP2040, USB-C only (no battery), 57 keys, built-in USB sound card
The wireless board (branch main: nRF52840 module, Li-Po) with the radio and the battery taken out; the RP2040 follows Raspberry Pi's 'Hardware design with RP2040' (the Pico's circuit). Differences from the wireless board:
1. USB only, no battery: no Ebyte E73 (nRF52840) module, no Bluetooth, no Li-Po cell, no charger (MCP73831), no power path (B5819W + SI2301), no power switch, no battery divider, no 32.768 kHz crystal, no antenna keep-out.
2. Raspberry Pi RP2040 instead of the module, with the minimum circuit of Raspberry Pi's 'Hardware design with RP2040' (the Pico's): 12 MHz crystal ABM8-272-T3 (the one Raspberry Pi qualified) with 2 x 15 pF and 1k in series on XOUT; W25Q128JV QSPI flash (16 MB) with a 10k pull-up on QSPI_SS; 100 n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
IOVDD 49's as in the design guide, IOVDD 10 / 33 sharing 1's / 42's through a tie under the package and DVDD 50 VREG_VOUT's 1 uF through the 1.1 V ring under it; 1 uF on VREG_VIN and VREG_VOUT; each within a few mm of its pin on the bottom layer; the internal regulator makes the 1.1 V core supply; 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
3. USB: hub port 3 goes to the RP2040's USB_DP / USB_DM through 27 ohm series resistors (as on the Pico and in the design guide), instead of the module's D+ / D-.
4. Programming: the RP2040's boot ROM is a USB drive (RPI-RP2) - no bootloader to flash with an SWD probe. A blank board starts in it; BOOT (SW101, QSPI_SS to GND through 1k) held while plugging the cable enters it again; RESET (SW102) pulls RUN low. The SWD pads stay for debugging.
5. 3.3 V regulator AP2112K-3.3 (the same as the wireless board) fed straight from VBUS: 1 uF in, 1 uF + 4.7 uF out; it also supplies the USB hub (V5 and VDD33 on 3.3 V, CH334 datasheet 6.4), so nothing but the regulator, the sound card's switch and the protection sits on VBUS.
6. VBUS protection at the receptacle: SMF5.0A TVS and a 4.7 uF bulk capacitor damped by 1 ohm (hot-plug ringing); VBUS divider 22k / 27k + 1 nF to GPIO29 (ADC3) for the firmware.
7. Status LED (red, Caps Lock) on an RP2040 GPIO, through 1k, as on the wireless board.
8. Test points: SWD (SWCLK, SWDIO, RESET, GND) in one row in front of the RP2040, 3V3 behind it, VBUS; no VBAT / VIN.
9. Sound card: the supply switch U8 is on a GPIO (GPIO12) with a 100k pull-down, as on the wireless board; the headphone amplifier's EN has its own GPIO (GPIO13) through 100k, held low by 1M (the wireless board delays it with an RC from the switch). The firmware turns the sound card on when the hos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
USB suspend and as soon as VBUS starts to fall.
USB-C (sink: 5.1k on each CC), ESD protection, VBUS TVS and damped bulk capacitor
3.3 V regulator AP2112K from VBUS (EN tied to VIN), also for the hub; 4.7 uF bulk at the RP2040
12 MHz crystal ABM8-272-T3 (CL 10 pF): 2 x 15 pF, 1k on XOUT; QSPI flash W25Q128JV, /CS pulled up
BOOT: QSPI_SS to GND through 1k (USB boot ROM); RESET: RUN to GND, 10k pull-up
RP2040 decoupling: 100 nF at IOVDD 1, 22, 42, 49, ADC_AVDD and DVDD 23 (USB_VDD shares 49's, IOVDD 10 / 33 1's / 42's, DVDD 50 VREG_VOUT's 1 uF); 1 uF at VREG_VIN and VREG_VOUT
VBUS sense: 22k / 27k + 1 nF to GPIO29 (ADC3)
Raspberry Pi RP2040 (1.1 V core from its own regulator: VREG_VOUT -> DVDD); USB through 27 ohm to the hub's port 3; status LED (Caps Lock) on a GPIO; SWD pads
Supplies: VBUS from the receptacle, codec supplies from VBUS through ferrite beads
USB hub CH334P (datasheet V2.91)
upstream from the receptacle, port 3 -> RP2040, port 2 -> codec
12 MHz crystal without load capacitors (inside the CH334)
RESET#, PGANG and ports 1 / 4 left open; V5 and VDD33 on the 3.3 V rail (datasheet 6.4)
Sound card CM108B (C-Media demo board v1.33 sheet 4, app notes v1.50); headset jack, CTIA
Open pins: internal pulls select headset mode (MODE low), 100 mA bus power (PWRSEL high),
internal ADC (ADSEL low), mixer on (MSEL high); R120-R123 strap them (10k). Jack: tip L, ring 1 R, ring 2 GND, sleeve mic.
Sound card supply: TPS22919 load switch, on from GPIO12 (soft start); headphone amplifier TPA6132A2 (DirectPath, 0 dB; -6 dB with JP3 closed), EN from GPIO13; headset jack, CTIA
Differences from the C-Media demo board:
1. Supply: VBUS through a TPS22919 load switch (soft start 1.3 ms, output discharge) to AUD_5V, ON from an RP2040 GPIO (on once the host has
configured the keyboard): the sound card's capacitors are charged slowly. A hard switch-on would dip VBUS enough to reset the hub (CH334 datasheet
6.1).
2. Headphones: a TPA6132A2 DirectPath amplifier after LOL / LOR (demo board: 100 uF + 39R straight to the jack): about 0 ohm output impedance, no
coupling capacitors, 0 dB gain (-6 dB with JP3 closed, for very sensitive earphones). Inputs single-ended through 1 uF (8 Hz); EN from an RP2040
GPIO through 100k (1M to ground): on 0.2 s after the supply, off in USB suspend (2 mA saved) and, when the cable is pulled, as soon as the firmware
sees VBUS fall, before the codec loses its supply (no click).
3. Microphone: bias 1.2k + 2.2k (demo board 2.2k + 8.2k, for PC microphones) for phone headsets (Android: 1.8-2.9 V through 2.2k); 1k in series before
MICIN against the step when a plug goes in.
4. The demo board's two 10 nF capacitors DVDD - DREG18 and DVDD - DREG33 ('close to IC', for ESD) are fitted; each AVDD pin (29, 34) has its own 100
